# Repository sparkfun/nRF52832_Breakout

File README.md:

SparkFun nRF52832 Breakout
========================================

[*SparkFun nRF52832 Breakout (WRL-13990)*](https://www.sparkfun.com/products/13990)

The nRF52832 is [Nordic Semiconductor's](https://www.nordicsemi.com/eng/Products/Bluetooth-low-energy/nRF52832) latest multiprotocol radio system-on-chip (SoC). It's half microcontroller, with a list of features including 32 configurable I/O pins, SPI, I<sup>2</sup>C, UART, PWM, ADC's, 512kB flash, and 64kB RAM. And, it's half 2.4GHz multiprotocol radio, supporting **Bluetooth low energy** (BLE), **ANT**, and Nordic's proprietary 2.4GHz ultra low-power wireless communication -- it even features on-chip NFC tag support.

SparkFun's [nRF52832 Breakout](https://www.sparkfun.com/products/13990) provides easy access to all of the chip's features. It breaks out all of the nRF52's I/O pins, provides a 32.768kHz RTC crystal, a user-programmable button and LED, and a trace antenna to send and receive those 2.4GHz transmissions. Plus, to make the chip as easy-to-flash as possible, the breakout comes pre-programmed with a **serial bootloader**.

Repository Contents
-------------------

* **/Documentation** - Data sheets, additional product information
* **/Firmware** - Serial bootloader source and hex files
* **/Hardware** - Eagle design files (.brd, .sch)
* **/Production** - Production panel files (.brd)

Documentation
--------------
* **[Arduino Hardware Definitions](https://github.com/sparkfun/Arduino_Boards/)** - Arduino cores and tools for the nRF52.
* **[Hookup Guide](https://learn.sparkfun.com/tutorials/nrf52832-breakout-board-hookup-guide)** - Basic hookup guide for the nRF52832 Breakout.
* **[SparkFun Fritzing repo](https://github.com/sparkfun/Fritzing_Parts)** - Fritzing diagrams for SparkFun products.

Product Versions
----------------
* [SparkFun nRF52832 Breakout (WRL-13990)](https://www.sparkfun.com/products/13990)- Initial release of the nRF52832 Breakout

Version History
---------------

License Information
-------------------

This product is _**open source**_! 

Please review the LICENSE.md file for license information. 

If you have any questions or concerns on licensing, please contact techsupport@sparkfun.com.

Distributed as-is; no warranty is given.

- Your friends at SparkFun.

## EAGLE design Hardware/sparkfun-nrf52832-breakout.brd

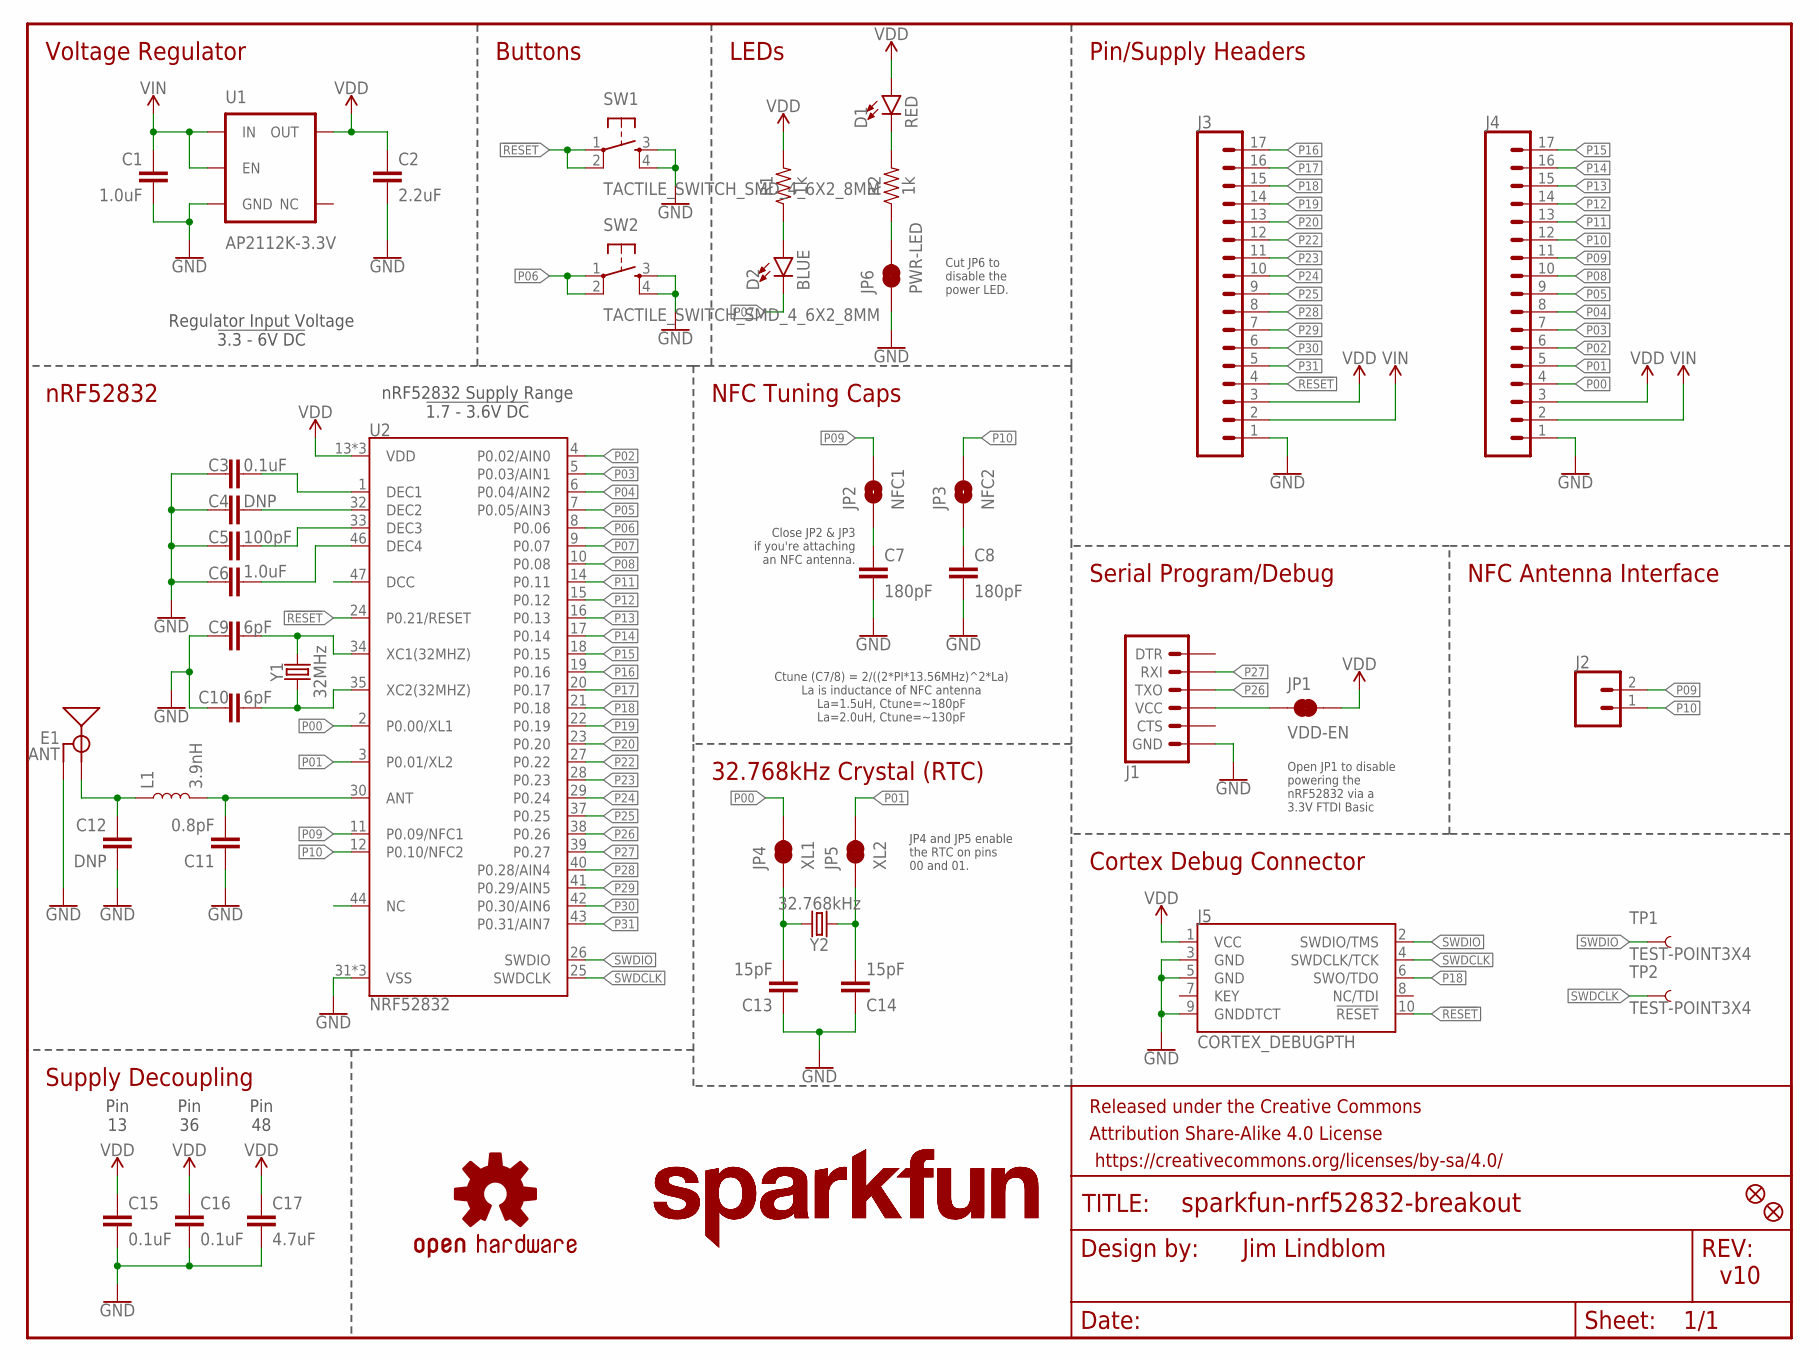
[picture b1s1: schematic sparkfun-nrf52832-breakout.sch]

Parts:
C1: 1.0uF; 0603
C2: 2.2uF; 0603
C3, C15, C16: 0.1uF; 0402
C4, C12: DNP; 0402
C5: 100pF; 0402
C6: 1.0uF; 0402
C7, C8: 180pF; 0603
C9, C10: 6pF; 0402
C11: 0.8pF; 0402
C13, C14: 15pF; 0402
C17: 4.7uF; 0603
D1: RED; LED-0603
D2: BLUE; LED-0603
E1: ANT; TRACE_ANTENNA_2.4GHZ_15.2MM
FD1, FD2: FIDUCIALUFIDUCIAL; FIDUCIAL-MICRO
FRAME1: FRAME-LETTER; CREATIVE_COMMONS
J1: ARDUINO_SERIAL_PROGRAMPTH; 1X06
J2: CONN_02PTH; 1X02
J3, J4: CONN_17; 1X17
J5: CORTEX_DEBUGPTH; 2X5-PTH-1.27MM
JP1: VDD-EN; SMT-JUMPER_2_NC_TRACE_SILK
JP2: NFC1; SMT-JUMPER_2_NO_SILK
JP3: NFC2; SMT-JUMPER_2_NO_SILK
JP4: XL1; PAD-JUMPER-2-NC_BY_TRACE_YES_SILK
JP5: XL2; PAD-JUMPER-2-NC_BY_TRACE_YES_SILK
JP6: PWR-LED; PAD-JUMPER-2-NC_BY_TRACE_YES_SILK
L1: 3.9nH; 0402
LOGO1: OSHW-LOGOMINI; OSHW-LOGO-MINI
LOGO2, LOGO3: SFE_LOGO_NAME.1_INCH; SFE_LOGO_NAME_.1
R1, R2: 1k; 0603
SW1, SW2: TACTILE_SWITCH_SMD_4_6X2_8MM; TACTILE_SWITCH_SMD_4.6X2.8MM
TP1, TP2: TEST-POINT3X4; PAD.03X.04
U1: AP2112K-3.3V; SOT23-5
U2: NRF52832; QFN48-6X6MM
Y1: 32MHz; CRYSTAL-SMD-2.0X1.6MM
Y2: 32.768kHz; CRYSTAL-SMD-3.2X1.5MM

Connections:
!RESET!: J3.4, J5.10 (!RESET), SW1.1, SW1.2, U2.24 (P0.21/RESET)
ANT: C11.2, L1.2, U2.30 (ANT)
DCC: U2.47 (DCC)
DEC1: C3.2, U2.1 (DEC1)
DEC2: C4.2, U2.32 (DEC2)
DEC3: C5.2, U2.33 (DEC3)
DEC4: C6.2, U2.46 (DEC4)
GND: C1.2, C2.2, C3.1, C4.1, C5.1, C6.1, C7.2, C8.2, C9.1, C10.2, C11.1, C12.2, C13.1, C14.1, C15.2, C16.2, C17.2, E1.GND, J1.6 (GND), J3.1, J4.1, J5.3 (GND), J5.5 (GND), J5.9 (GNDDTCT), JP6.1, SW1.3, SW1.4, SW2.3, SW2.4, U1.2 (GND), U2.31 (VSS), U2.45 (VSS), U2.EP (VSS)
unnamed: JP6.2, R2.1
unnamed: C13.2, JP4.1, Y2.P$2 (2)
unnamed: C14.2, JP5.1, Y2.P$1 (1)
unnamed: C12.1, E1.ANT (SIGNAL), L1.1
unnamed: D1.C, R2.2
unnamed: J1.4 (VCC), JP1.1
unnamed: D2.A, R1.1
NC: U2.44 (NC)
NFC1: C7.1, JP2.1
NFC2: C8.1, JP3.1
P00: J4.4, JP4.2, U2.2 (P0.00/XL1)
P01: J4.5, JP5.2, U2.3 (P0.01/XL2)
P02: J4.6, U2.4 (P0.02/AIN0)
P03: J4.7, U2.5 (P0.03/AIN1)
P04: J4.8, U2.6 (P0.04/AIN2)
P05: J4.9, U2.7 (P0.05/AIN3)
P06: SW2.1, SW2.2, U2.8 (P0.06)
P07: D2.C, U2.9 (P0.07)
P08: J4.10, U2.10 (P0.08)
P09: J2.2, J4.11, JP2.2, U2.11 (P0.09/NFC1)
P10: J2.1, J4.12, JP3.2, U2.12 (P0.10/NFC2)
P11: J4.13, U2.14 (P0.11)
P12: J4.14, U2.15 (P0.12)
P13: J4.15, U2.16 (P0.13)
P14: J4.16, U2.17 (P0.14)
P15: J4.17, U2.18 (P0.15)
P16: J3.17, U2.19 (P0.16)
P17: J3.16, U2.20 (P0.17)
P18: J3.15, J5.6 (SWO/TDO), U2.21 (P0.18)
P19: J3.14, U2.22 (P0.19)
P20: J3.13, U2.23 (P0.20)
P22: J3.12, U2.27 (P0.22)
P23: J3.11, U2.28 (P0.23)
P24: J3.10, U2.29 (P0.24)
P25: J3.9, U2.37 (P0.25)
P26: J1.3 (TXO), U2.38 (P0.26)
P27: J1.2 (RXI), U2.39 (P0.27)
P28: J3.8, U2.40 (P0.28/AIN4)
P29: J3.7, U2.41 (P0.29/AIN5)
P30: J3.6, U2.42 (P0.30/AIN6)
P31: J3.5, U2.43 (P0.31/AIN7)
SWDCLK: J5.4 (SWDCLK/TCK), TP2.P$1, U2.25 (SWDCLK)
SWDIO: J5.2 (SWDIO/TMS), TP1.P$1, U2.26 (SWDIO)
VDD: C2.1, C15.1, C16.1, C17.1, D1.A, J3.3, J4.3, J5.1 (VCC), JP1.2, R1.2, U1.5 (OUT), U2.13 (VDD), U2.36 (VDD), U2.48 (VDD)
VIN: C1.1, J3.2, J4.2, U1.1 (IN), U1.3 (EN)
XC1: C9.2, U2.34 (XC1(32MHZ)), Y1.3 (2)
XC2: C10.1, U2.35 (XC2(32MHZ)), Y1.1

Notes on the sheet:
Pin 13
Pin 36
Pin 48
v10
Jim Lindblom
Ctune (C7/8) = 2/((2*PI*13.56MHz)^2*La) La is inductance of NFC antenna La=1.5uH, Ctune=~180pF La=2.0uH, Ctune=~130pF
Voltage Regulator
Buttons
LEDs
Pin/Supply Headers
nRF52832
32.768kHz Crystal (RTC)
Supply Decoupling
NFC Tuning Caps
Cortex Debug Connector
Serial Program/Debug
NFC Antenna Interface
Open JP1 to disable powering the nRF52832 via a 3.3V FTDI Basic
Close JP2 & JP3 if you're attaching an NFC antenna.
JP4 and JP5 enable the RTC on pins 00 and 01.
Regulator Input Voltage !3.3 - 6V DC!
nRF52832 Supply Range !1.7 - 3.6V DC!
Cut JP6 to disable the power LED.

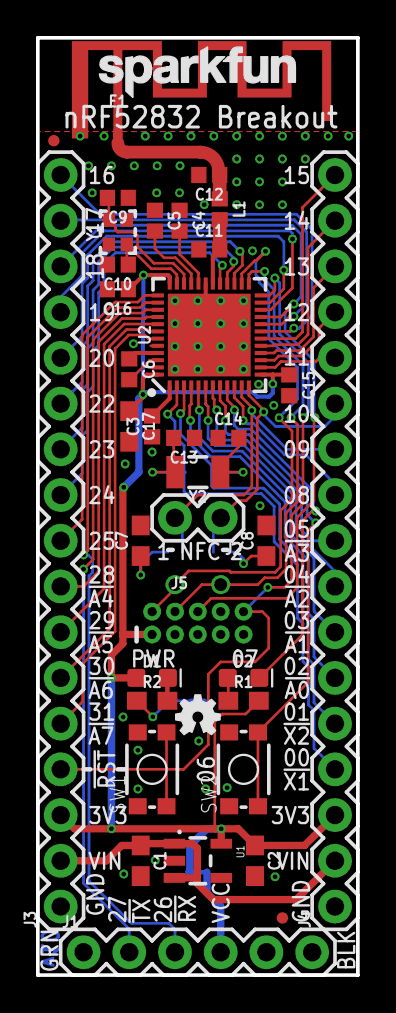
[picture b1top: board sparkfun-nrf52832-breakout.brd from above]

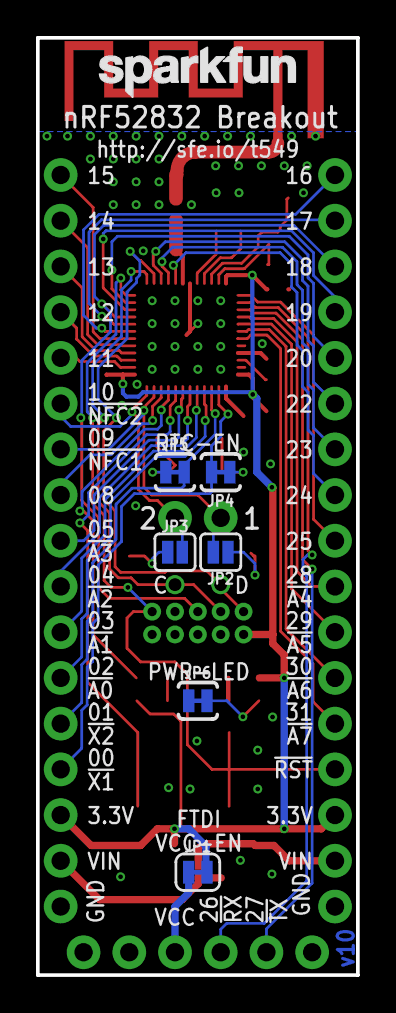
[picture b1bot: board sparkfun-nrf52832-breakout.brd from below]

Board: 2 copper layers, 17.8 x 52.1 mm, 48 parts (9 on the bottom side), 53 nets.

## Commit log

2016-07-18 initial commit of hardware design
2016-07-18 Adding pertinent documentation.
2016-07-18 Schematic cleanup.
2016-07-18 Adding cut-jumper to the power LED.
2016-07-19 Updates after running checklist.
2016-07-19 Adding test points to swd pins, stubs to NC QFN pins.
2016-08-22 Moving test points to bottom, switching to micro fids, silk nudging.
2016-08-23 Making SWD test points larger drill diameter.
2016-08-24 Defaulting JP1 to closed.
2016-08-24 Reducing nRF52832's center pad tcream to 33%.
2016-08-24 Fixing version number on PCB.
2016-08-25 Adjusting silk.
2016-11-17 Adding bootloader source and hex, updating readme.
2016-11-18 Adding armgcc makefile
2016-11-22 Adding of Values to SW1 and SW2
    3D Model Modification
2017-02-07 Adding custom_board.h, and cleaning up Makefile to use relative paths.
2017-02-07 Removing extra, unused makefile.
2017-02-07 Adding more content re: compiling to the README.
2017-02-07 Removing unused linker script and dfu_ble_svc source
2021-04-12 New .hex file with clock source from internal RC
    The only change in the DFU firmware was made at the source of the clock for the SoftDevice application. With the original, custom boards without the 32.768 crystal could not use the pre-compiled Spar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
    The "nRF52832 Breakout Board Hookup Guide" induces to understand that it could be without:
    "The nRF52832 Breakout equips the chip with a 32.768kHz crystal -- connected to GPIO pins 0 and 1. Unfortunately, those pins make up a quarter of the available ADC inputs. So, if your application doe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

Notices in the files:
parts and their libraries:
SparkFun-Aesthetics: Licensing: Creative Commons ShareAlike 4.0 International - https://creativecommons.org/licenses/by-sa/4.0
SparkFun-Aesthetics: Released under the Creative Commons Attribution Share-Alike 4.0 License
SparkFun-Aesthetics: https://creativecommons.org/licenses/by-sa/4.0
